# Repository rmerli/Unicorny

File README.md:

# Unicorny
It is a unibody ergonomic keyboard inspired by the ferris-sweep (34 keys).
The aim of this keyboard is to have a layout as close as possbile to the ferris-sweep but in a unibody frame, 
to improve connection stability and because I found it easier to carry around.

## Features
- Wired/wireless
- Hotswap choc v1
- ProMicro footprint (designed with ninenano v2 in mind)
- Oled screen (optional)
- Power Switch (Wireless)

## Firmware
I choose Zmk and the config can be found [here](https://github.com/Riccardo-merli94/zmk/tree/main/app/boards/shields/unicorny).
I built the firmware locally, so the repository contains a fork of zmk, if you want to build it using the github actions, you'll need to follow the zmk doc.

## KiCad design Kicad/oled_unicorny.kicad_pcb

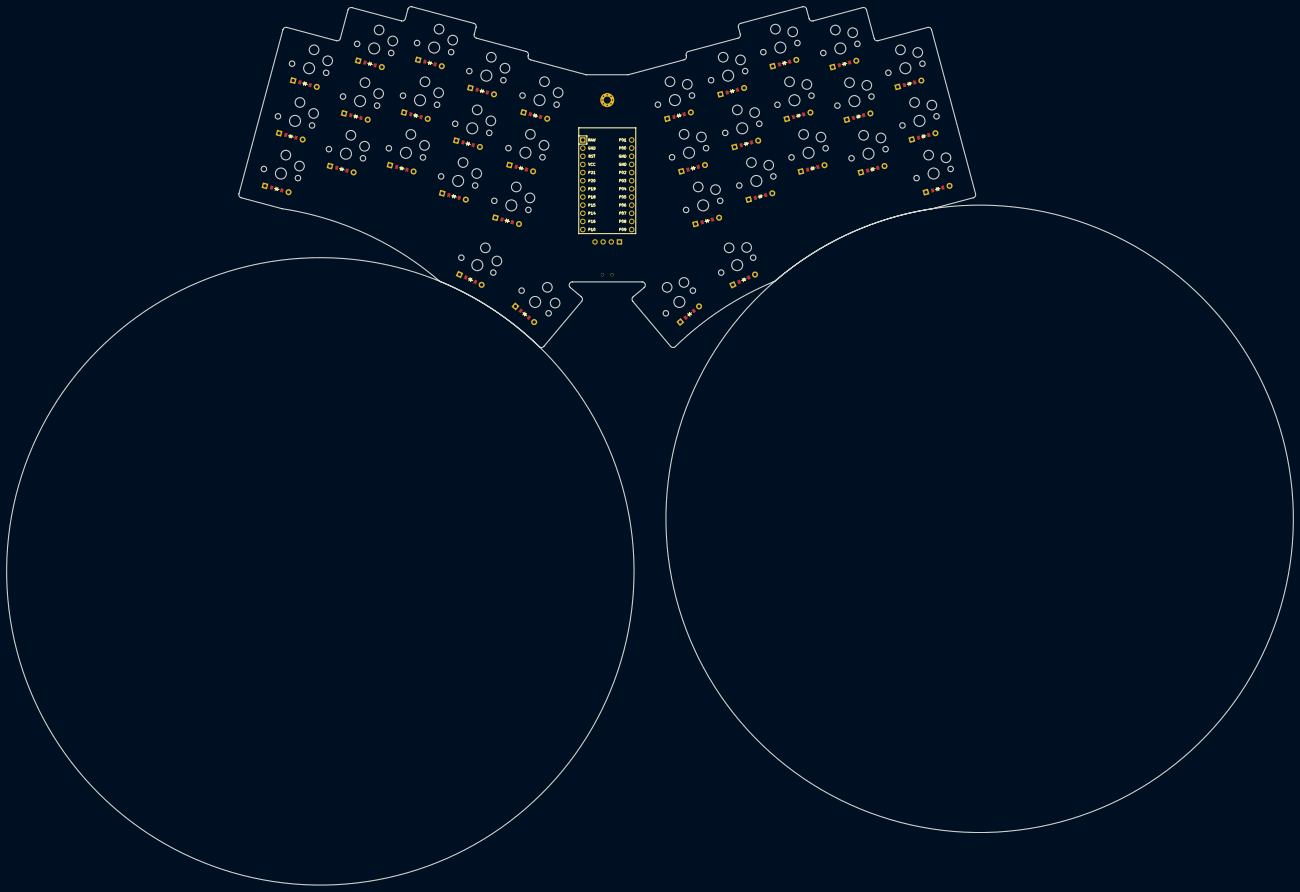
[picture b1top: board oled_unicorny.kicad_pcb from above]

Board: 2 copper layers, 401.3 x 274.0 mm, 74 parts (0 on the bottom side), 52 nets, no tracks yet.

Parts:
D1, D2, D3, D4, D5, D6, D7, D8, D9, D10, D11, D12, D13, D14, D15, D16, D17, D18, D19, D20, D21, D22, D23, D24, D25, D26, D27, D28, D29, D30, D31, D32, D33, D34: ComboDiode
MCU1: ProMicro
OLED1: OLED; OLED_headers
PAD1, PAD2: SMDPad
S1, S2, S3, S4, S5, S6, S7, S8, S9, S10, S11, S12, S13, S14, S15, S16, S17, S18, S19, S20, S21, S22, S23, S24, S25, S26, S27, S28, S29, S30, S31, S32, S33, S34: PG1350
T1: SPDT_C128955
_1: MountingHole_2.2mm_M2_Pad_Via

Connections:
B+: PAD1.1, T1.2
GND: MCU1.2, MCU1.15, MCU1.16, OLED1.1, PAD2.1
P0: MCU1.14, S10.1, S11.1, S12.1, S16.1, S27.1, S28.1, S29.1, S33.1
P1: MCU1.13, S13.1, S14.1, S15.1, S17.1, S30.1, S31.1, S32.1, S34.1
P2: MCU1.17, OLED1.4
P3: MCU1.18, OLED1.3
P6: D20.1, D23.1, D26.1, D29.1, D32.1, MCU1.21
P7: D19.1, D22.1, D25.1, D28.1, D31.1, MCU1.22
P8: D18.1, D21.1, D24.1, D27.1, D30.1, MCU1.23
P14: D1.1, D4.1, D7.1, D10.1, D13.1, MCU1.10
P15: D2.1, D5.1, D8.1, D11.1, D14.1, MCU1.9
P16: D16.1, D17.1, D33.1, D34.1, MCU1.11
P18: D3.1, D6.1, D9.1, D12.1, D15.1, MCU1.8
P19: MCU1.7, S1.1, S2.1, S3.1, S18.1, S19.1, S20.1
P20: MCU1.6, S4.1, S5.1, S6.1, S21.1, S22.1, S23.1
P21: MCU1.5, S7.1, S8.1, S9.1, S24.1, S25.1, S26.1
RAW: MCU1.1, T1.1
VCC: MCU1.4, OLED1.2
index_bottom: D10.2, S10.2
index_home: D11.2, S11.2
index_top: D12.2, S12.2
inner_bottom: D13.2, S13.2
inner_home: D14.2, S14.2
inner_top: D15.2, S15.2
middle_bottom: D7.2, S7.2
middle_home: D8.2, S8.2
middle_top: D9.2, S9.2
mirror_index_bottom: D27.2, S27.2
mirror_index_home: D28.2, S28.2
mirror_index_top: D29.2, S29.2
mirror_inner_bottom: D30.2, S30.2
mirror_inner_home: D31.2, S31.2
mirror_inner_top: D32.2, S32.2
mirror_middle_bottom: D24.2, S24.2
mirror_middle_home: D25.2, S25.2
mirror_middle_top: D26.2, S26.2
mirror_pinky_bottom: D18.2, S18.2
mirror_pinky_home: D19.2, S19.2
mirror_pinky_top: D20.2, S20.2
mirror_reachy_fan: D34.2, S34.2
mirror_ring_bottom: D21.2, S21.2
mirror_ring_home: D22.2, S22.2
mirror_ring_top: D23.2, S23.2
mirror_tucky_fan: D33.2, S33.2
pinky_bottom: D1.2, S1.2
pinky_home: D2.2, S2.2
pinky_top: D3.2, S3.2
reachy_fan: D17.2, S17.2
ring_bottom: D4.2, S4.2
ring_home: D5.2, S5.2
ring_top: D6.2, S6.2
tucky_fan: D16.2, S16.2

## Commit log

2023-05-06 init
2023-05-06 added image
2023-05-06 rotated image
2023-11-15 added ergogen config for a 40 keys layout
2023-11-25 added 40 keys variant
2023-12-07 added board cad file
2023-12-07 added stls and f360 project
2024-02-26 Added 40 keys picture
2024-02-26 Added 40 keys
2024-02-26 Added 40k image
2024-02-29 Update README.md
    Fixed typo
